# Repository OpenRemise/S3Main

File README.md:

# S3Main

<a href="https://openremise.at">
<picture>
  <source media="(prefers-color-scheme: dark)" srcset="https://github.com/OpenRemise/.github/raw/master/data/icons/icon_dark.svg">
  
</picture>
</a>

The S3Main is the first officially supported [OpenRemise](https://openremise.at) board.

### Features
- WiFi-capable ESP32-S3 SoC
- 10-22V DC supply
- Reverse polarity protection
- Single track output
- Adjustable current limits 0.5, 1.3, 2.7 and 4.1A
- [SUSI](https://normen.railcommunity.de/RCN-600.pdf) interface
- USB-C interface
- RailCom detector

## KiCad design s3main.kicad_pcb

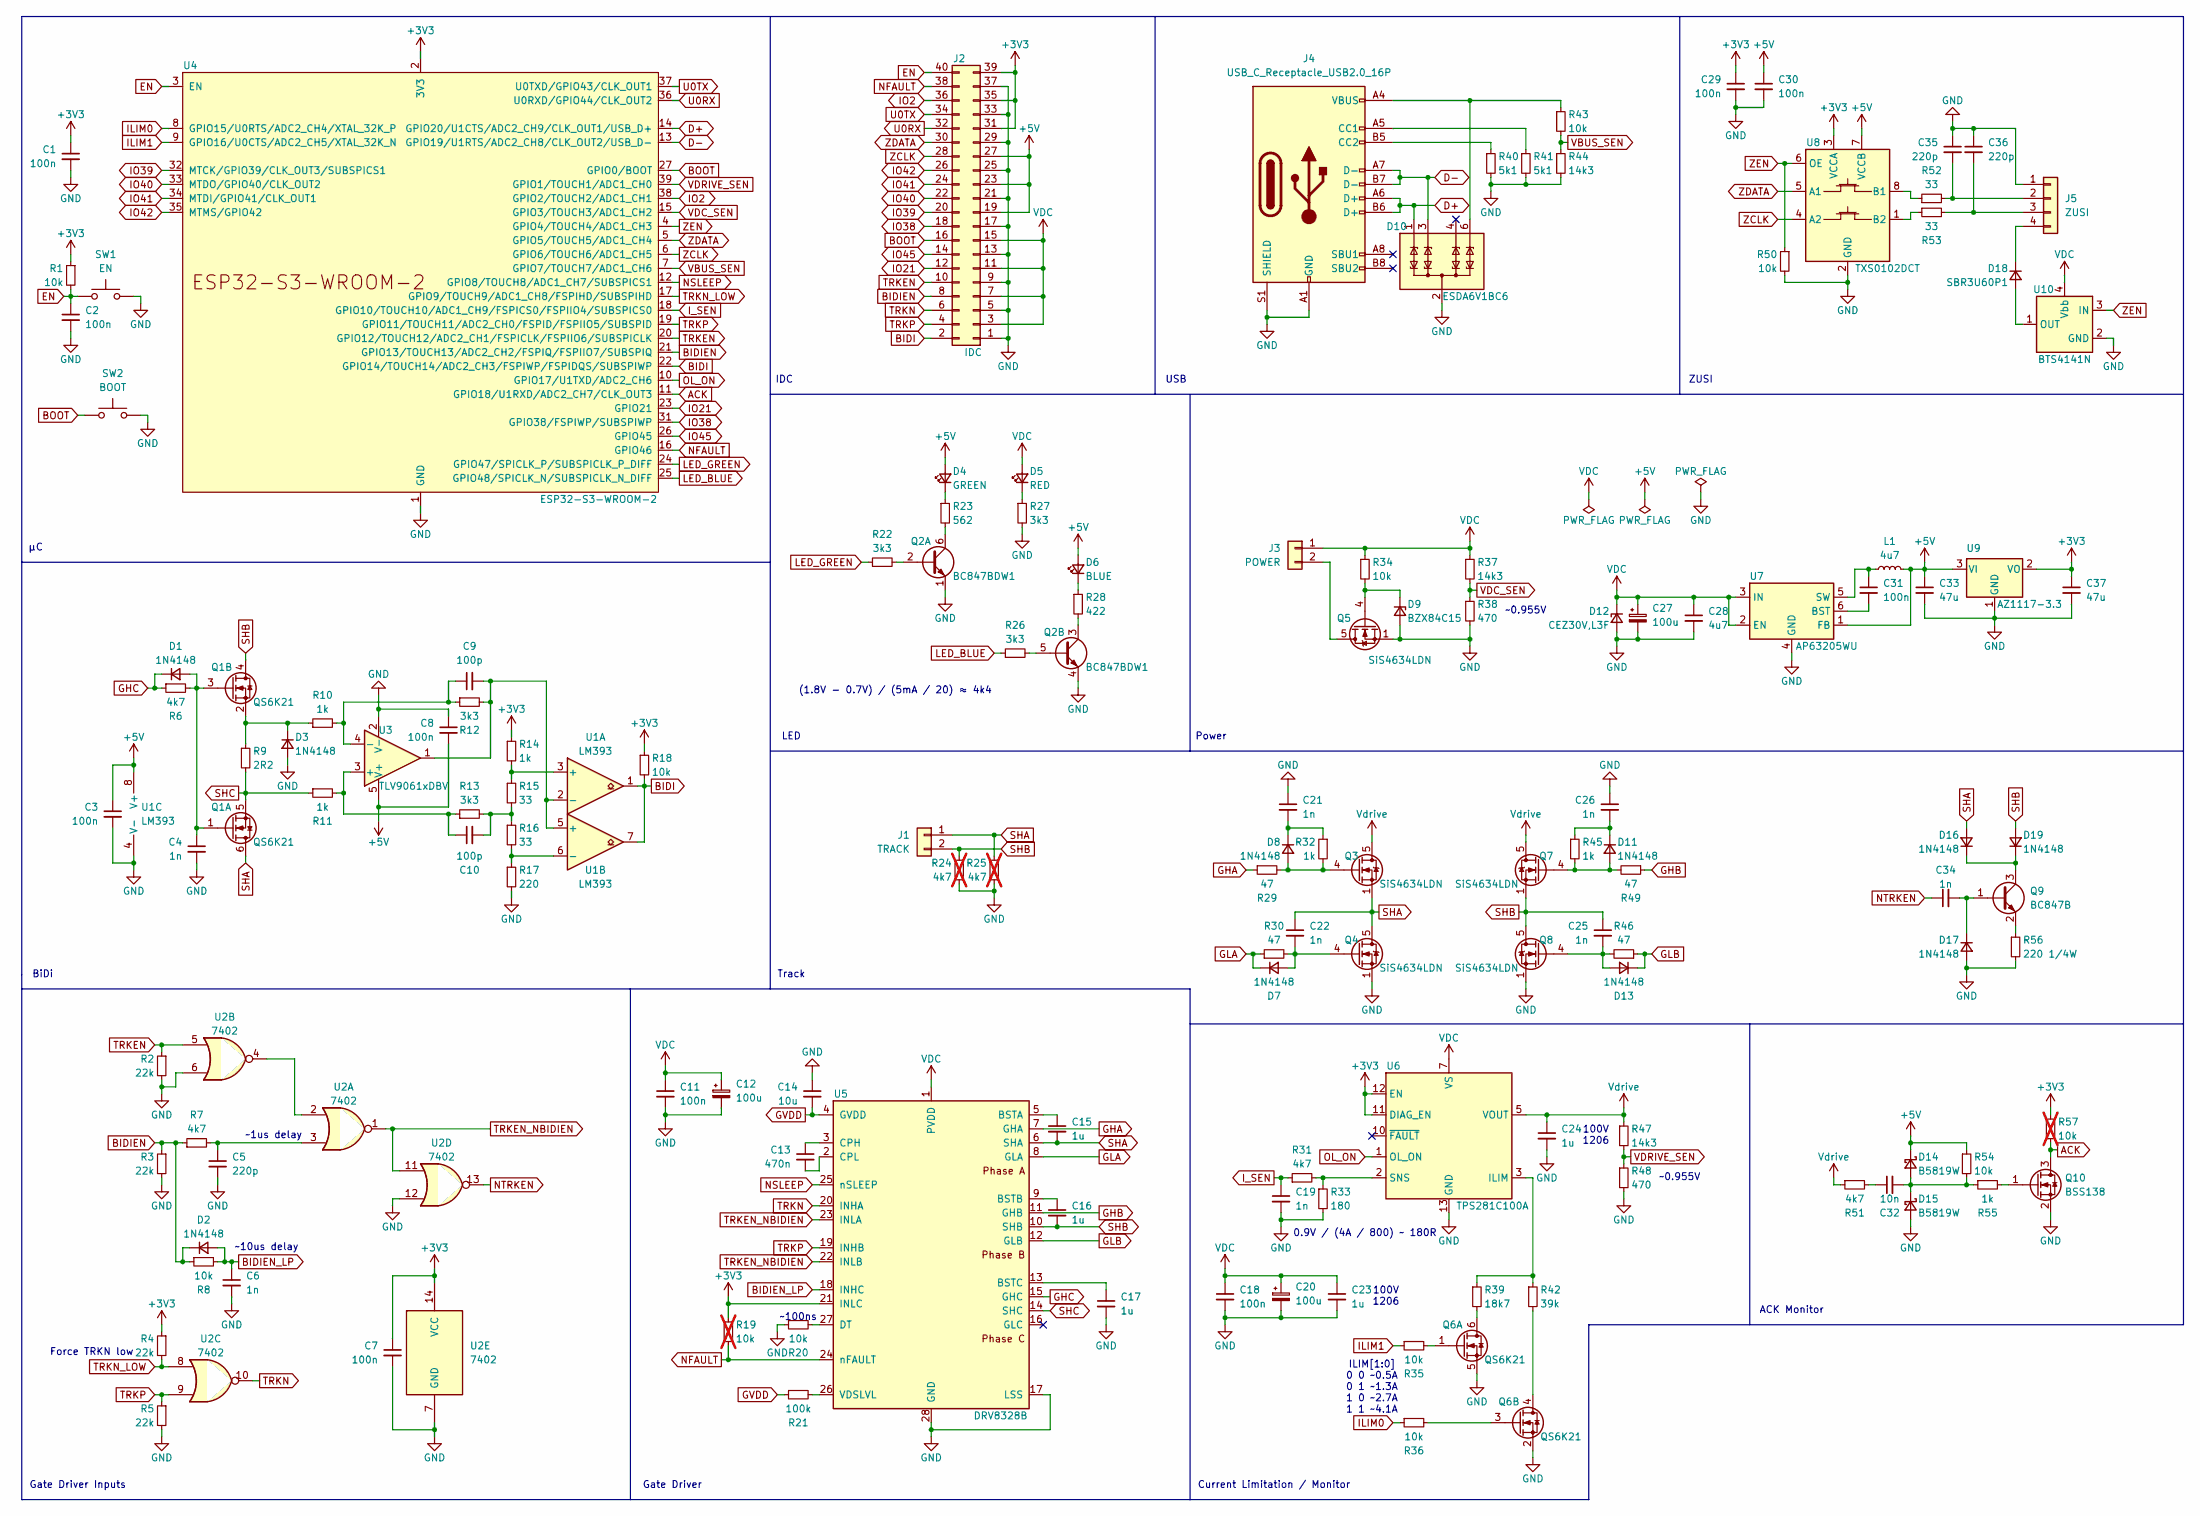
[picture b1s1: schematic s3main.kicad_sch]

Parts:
C1, C2, C3, C7, C8, C11, C18, C29, C30, C31: 100n; C_0402_1005Metric
C4, C6, C19, C21, C22, C25, C26, C34: 1n; C_0402_1005Metric
C5, C35, C36: 220p; C_0402_1005Metric
C9, C10: 100p; C_0402_1005Metric
C12, C20, C27: 100u; CP_Elec_6.3x7.7
C13: 470n; C_1206_3216Metric
C14: 10u; C_1206_3216Metric
C15, C16, C17, C23, C24: 1u; C_1206_3216Metric
C28: 4u7; C_1206_3216Metric
C32: 10n; C_1206_3216Metric
C33, C37: 47u; C_1206_3216Metric
D1, D2, D3, D7, D8, D11, D13, D16, D17, D19: 1N4148; D_SOD-523
D4: GREEN; D_0402_1005Metric
D5: RED; D_0402_1005Metric
D6: BLUE; D_0402_1005Metric
D9: BZX84C15; SOT-23
D10: ESDA6V1BC6; SOT-23-6
D12: CEZ30V,L3F; D_SOD-523
D14, D15: B5819W; D_SOD-123
D18: SBR3U60P1; D_PowerDI-123
J1: TRACK; PhoenixContact_MC_1,5_2-G-3.5_1x02_P3.50mm_Horizontal
J2: IDC; IDC-Header_2x20_P2.54mm_Vertical_SMD
J3: POWER; PhoenixContact_MC_1,5_2-G-5.08_1x02_P5.08mm_Horizontal
J4: USB_C_Receptacle_USB2.0_16P; USB_C_Receptacle_GCT_USB4105-xx-A_16P_TopMnt_Horizontal
J5: ZUSI; JST_SH_SM04B-SRSS-TB_1x04-1MP_P1.00mm_Horizontal
L1: 4u7; L_0805_2012Metric
Q1, Q6: QS6K21; TSOT-23-6
Q2: BC847BDW1; SOT-363_SC-70-6
Q3, Q4, Q5, Q7, Q8: SiS4634LDN; Vishay_PowerPAK_1212-8_Single
Q9: BC847B; SOT-23
Q10: BSS138; SOT-23
R1, R8, R18, R20, R34, R35, R36, R43, R50, R54: 10k; R_0402_1005Metric
R2, R3, R4, R5: 22k; R_0402_1005Metric
R6, R7, R31, R51: 4k7; R_0402_1005Metric
R9: 2R2; R_0805_2012Metric_Pad1.20x1.40mm_HandSolder
R10, R11, R14, R32, R45, R55: 1k; R_0402_1005Metric
R12, R13, R22, R26, R27: 3k3; R_0402_1005Metric
R15, R16, R52, R53: 33; R_0402_1005Metric
R17: 220; R_0402_1005Metric
R19, R57: 10k; R_0402_1005Metric; not fitted
R21: 100k; R_0402_1005Metric
R23: 562; R_0402_1005Metric
R24, R25: 4k7; R_0805_2012Metric_Pad1.20x1.40mm_HandSolder; not fitted
R28: 422; R_0402_1005Metric
R29, R30, R46, R49: 47; R_0402_1005Metric
R33: 180; R_0402_1005Metric
R37, R44, R47: 14k3; R_0402_1005Metric
R38, R48: 470; R_0402_1005Metric
R39: 18k7; R_0402_1005Metric
R40, R41: 5k1; R_0402_1005Metric
R42: 39k; R_0402_1005Metric
R56: 220 1/4W; R_0402_1005Metric
SW1: EN; SW_SPST_EVPBF
SW2: BOOT; SW_SPST_EVPBF
U1: LM393; SOIC-8_3.9x4.9mm_P1.27mm
U2: 7402; TSSOP-14_4.4x5mm_P0.65mm
U3: TLV9061xDBV; SOT-23-5
U4: ESP32-S3-WROOM-2
U5: DRV8328B; QFN-28-1EP_4x4mm_P0.4mm_EP2.6x2.6mm_ThermalVias
U6: TPS281C100A; WSON-12-1EP_4x4mm_P0.5mm_EP2.6x3mm_ThermalVias
U7: AP63205WU; TSOT-23-6
U8: TXS0102DCT; SSOP-8_2.95x2.8mm_P0.65mm
U9: AZ1117-3.3; SOT-89-3
U10: BTS4141N; SOT-223

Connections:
+3V3: C1.1, C7.1, C29.1, C37.1, J2.31, J2.35, J2.39, R1.1, R4.1, R14.1, R18.1, R19.1, R57.1, U2.14 (VCC), U4.2 (3V3), U5.21 (INLC), U6.11 (DIAG_EN), U6.12 (EN), U8.3 (VCCA), U9.2 (VO)
+5V: C3.1, C8.2, C30.1, C33.1, D4.2 (A), D6.2 (A), D14.1 (K), J2.19, J2.23, J2.27, L1.2, R54.1, U1.8 (V+), U3.5 (V+), U7.1 (FB), U8.7 (VCCB), U9.3 (VI)
ACK: Q10.3 (D), R57.2, U4.11 (GPIO18/U1RXD/ADC2_CH7/CLK_OUT3)
BIDI: J2.2, R18.2, U1.1, U1.7, U4.22 (GPIO14/TOUCH14/ADC2_CH3/FSPIWP/FSPIDQS/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)
BIDIEN: D2.1 (K), J2.8, R3.1, R7.1, R8.1, U4.21 (GPIO13/TOUCH13/ADC2_CH2/FSPIQ/FSPIIO7/S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)
BIDIEN_LP: C6.1, D2.2 (A), R8.2, U5.18 (INHC)
BOOT: J2.16, SW2.1, U4.27 (GPIO0/BOOT)
D+: D10.1 (TVS1), J4.A6 (D+), J4.B6 (D+), U4.14 (GPIO20/U1CTS/ADC2_CH9/CLK_OUT1/USB_D+)
D-: D10.3 (TVS2), J4.A7 (D-), J4.B7 (D-), U4.13 (GPIO19/U1RTS/ADC2_CH8/CLK_OUT2/USB_D-)
EN: C2.1, J2.40, R1.2, SW1.1, U4.3 (EN)
GHA: R29.1, U5.7 (GHA)
GHB: R49.1, U5.11 (GHB)
GHC: D1.1 (K), R6.1, U5.15 (GHC)
GLA: D7.1 (K), R30.1, U5.8 (GLA)
GLB: D13.1 (K), R46.1, U5.12 (GLB)
GND: C1.2, C2.2, C3.2, C4.2, C5.2, C6.2, C7.2, C8.1, C11.2, C12.2, C14.1, C17.2, C18.2, C19.2, C20.2, C21.1, C23.2, C24.2, C26.1, C27.2, C28.2, C29.2, C30.2, C33.2, C35.1, C36.1, C37.2, D3.2 (A), D9.2 (A), D10.2 (COM), D10.5 (COM), D12.2 (A), D15.2 (A), D17.2 (A), J2.1, J2.5, J2.9, J2.13, J2.17, J2.21, J2.25, J2.29, J2.33, J2.37, J4.A1 (GND), J4.A12 (GND), J4.B1 (GND), J4.B12 (GND), J4.S1 (SHIELD), J5.1, Q2.1 (E1), Q2.4 (E2), Q4.1 (S), Q4.2 (S), Q4.3 (S), Q5.1 (S), Q5.2 (S), Q5.3 (S), Q6.2 (S), Q6.5 (S), Q8.1 (S), Q8.2 (S), Q8.3 (S), Q10.2 (S), R2.2, R3.2, R5.2, R17.2, R20.1, R24.2, R25.2, R27.2, R33.2, R38.2, R40.2, R41.2, R44.2, R48.2, R50.2, R56.2, SW1.2, SW2.2, U1.4 (V-), U2.6, U2.7 (GND), U2.12, U3.2 (V-), U4.1 (GND), U4.40 (GND), U4.41 (GND), U5.17 (LSS), U5.28 (GND), U5.29 (GND), U6.13 (GND), U7.4 (GND), U8.2 (GND), U9.1 (GND), U10.2 (GND)
GVDD: C14.2, R21.1, U5.4 (GVDD)
ILIM0: R36.1, U4.8 (GPIO15/U0RTS/ADC2_CH4/XTAL_32K_P)
ILIM1: R35.1, U4.9 (GPIO16/U0CTS/ADC2_CH5/XTAL_32K_N)
IO2: J2.36, U4.38 (GPIO2/TOUCH2/ADC1_CH1)
IO21: J2.12, U4.23 (GPIO21)
IO38: J2.18, U4.31 (GPIO38/FSPIWP/SUBSPIWP)
IO39: J2.20, U4.32 (MTCK/GPIO39/CLK_OUT3/SUBSPICS1)
IO40: J2.22, U4.33 (MTDO/GPIO40/CLK_OUT2)
IO41: J2.24, U4.34 (MTDI/GPIO41/CLK_OUT1)
IO42: J2.26, U4.35 (MTMS/GPIO42)
IO45: J2.14, U4.26 (GPIO45)
I_SEN: C19.1, R31.1, U4.18 (GPIO10/TOUCH10/ADC1_CH9/FSPICS0/FSPIIO4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)
LED_BLUE: R26.1, U4.25 (GPIO48/SPICLK_N/SUBSPICLK_N_DIFF)
LED_GREEN: R22.1, U4.24 (GPIO47/SPICLK_P/SUBSPICLK_P_DIFF)
NFAULT: J2.38, R19.2, U4.16 (GPIO46), U5.24 (nFAULT)
NSLEEP: U4.12 (GPIO8/TOUCH8/ADC1_CH7/SUBSPICS1), U5.25 (nSLEEP)
NTRKEN: C34.1, U2.13
unnamed: C5.1, R7.2, U2.3
unnamed: C10.2, R13.2, R15.2, R16.1
unnamed: C32.1, R51.2
unnamed: C4.1, D1.2 (A), Q1.1 (G), Q1.3 (G), R6.2
unnamed: D3.1 (K), Q1.2 (S), R9.1, R10.1
unnamed: D4.1 (K), R23.1
unnamed: D5.1 (K), R27.1
unnamed: D6.1 (K), R28.1
unnamed: C22.2, D7.2 (A), Q4.4 (G), R30.2
unnamed: D8.2 (A), Q3.4 (G), R29.2, R32.2
unnamed: C21.2, D8.1 (K), R32.1
unnamed: D9.1 (K), Q5.4 (G), R34.2
unnamed: D10.6 (TVS4), J4.A4 (VBUS), J4.A9 (VBUS), J4.B4 (VBUS), J4.B9 (VBUS), R43.1
unnamed: D11.2 (A), Q7.4 (G), R45.2, R49.2
unnamed: C26.2, D11.1 (K), R45.1
unnamed: C25.2, D13.2 (A), Q8.4 (G), R46.2
unnamed: C32.2, D14.2 (A), D15.1 (K), R54.2, R55.1
unnamed: D16.1 (K), D19.1 (K), Q9.3 (C)
unnamed: C34.2, D17.1 (K), Q9.1 (B)
unnamed: D18.2 (A), U10.1 (OUT)
unnamed: D18.1 (K), J5.4
unnamed: J3.2, Q5.5 (D)
unnamed: J4.A5 (CC1), R41.1
unnamed: J4.B5 (CC2), R40.1
unnamed: C35.2, J5.2, R52.2
unnamed: C36.2, J5.3, R53.2
unnamed: Q2.2 (B1), R22.2
unnamed: Q2.6 (C1), R23.2
unnamed: Q2.5 (B2), R26.2
unnamed: Q2.3 (C2), R28.2
unnamed: Q6.6 (D), R39.2
unnamed: Q6.1 (G), R35.2
unnamed: Q6.4 (D), R42.2
unnamed: Q6.3 (G), R36.2
unnamed: Q9.2 (E), R56.1
unnamed: Q10.1 (G), R55.2
unnamed: R14.2, R15.1, U1.3 (+)
unnamed: C9.2, R12.2, U1.2 (-), U1.5 (+), U3.1
unnamed: R16.2, R17.1, U1.6 (-)
unnamed: U2.2, U2.4
unnamed: C10.1, R11.2, R13.1, U3.3 (+)
unnamed: C9.1, R10.2, R12.1, U3.4 (-)
unnamed: C15.1, U5.5 (BSTA)
unnamed: C16.1, U5.9 (BSTB)
unnamed: C17.1, U5.13 (BSTC)
unnamed: C13.1, U5.3 (CPH)
unnamed: C13.2, U5.2 (CPL)
unnamed: R20.2, U5.27 (DT)
unnamed: R21.2, U5.26 (VDSLVL)
unnamed: R39.1, R42.1, U6.3 (ILIM)
unnamed: R31.2, R33.1, U6.2 (SNS)
unnamed: C31.2, U7.6 (BST)
unnamed: C31.1, L1.1, U7.5 (SW)
unnamed: R52.1, U8.8 (B1)
unnamed: R53.1, U8.1 (B2)
OL_ON: U4.10 (GPIO17/U1TXD/ADC2_CH6), U6.1 (OL_ON)
SHA: C15.2, C22.1, D16.2 (A), J1.1, Q1.6 (D), Q3.1 (S), Q3.2 (S), Q3.3 (S), Q4.5 (D), R25.1, U5.6 (SHA)
SHB: C16.2, C25.1, D19.2 (A), J1.2, Q1.4 (D), Q7.1 (S), Q7.2 (S), Q7.3 (S), Q8.5 (D), R24.1, U5.10 (SHB)
SHC: Q1.5 (S), R9.2, R11.1, U5.14 (SHC)
TRKEN: J2.10, R2.1, U2.5, U4.20 (GPIO12/TOUCH12/ADC2_CH1/FSPICLK/FSPIIO6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)
TRKEN_NBIDIEN: U2.1, U2.11, U5.22 (INLB), U5.23 (INLA)
TRKN: J2.6, U2.10, U5.20 (INHA)
TRKN_LOW: R4.2, U2.8, U4.17 (GPIO9/TOUCH9/ADC1_CH8/FSPIHD/SUBSPIHD)
TRKP: J2.4, R5.1, U2.9, U4.19 (GPIO11/TOUCH11/ADC2_CH0/FSPID/FSPIIO5/S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), U5.19 (INHB)
U0RX: J2.32, U4.36 (U0RXD/GPIO44/CLK_OUT2)
U0TX: J2.34, U4.37 (U0TXD/GPIO43/CLK_OUT1)
VBUS_SEN: R43.2, R44.1, U4.7 (GPIO7/TOUCH7/ADC1_CH6)
VDC: C11.1, C12.1, C18.1, C20.1, C23.1, C27.1, C28.1, D5.2 (A), D12.1 (K), J2.3, J2.7, J2.11, J2.15, J3.1, R34.1, R37.1, U5.1 (PVDD), U6.7 (VS), U6.8 (VS), U7.2 (EN), U7.3 (IN), U10.4 (Vbb)
VDC_SEN: R37.2, R38.1, U4.15 (GPIO3/TOUCH3/ADC1_CH2)
VDRIVE_SEN: R47.2, R48.1, U4.39 (GPIO1/TOUCH1/ADC1_CH0)
Vdrive: C24.1, Q3.5 (D), Q7.5 (D), R47.1, R51.1, U6.5 (VOUT), U6.6 (VOUT)
ZCLK: J2.28, U4.6 (GPIO6/TOUCH6/ADC1_CH5), U8.4 (A2)
ZDATA: J2.30, U4.5 (GPIO5/TOUCH5/ADC1_CH4), U8.5 (A1)
ZEN: R50.1, U4.4 (GPIO4/TOUCH4/ADC1_CH3), U8.6 (OE), U10.3 (IN)

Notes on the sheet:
Force TRKN low
~1us delay
IDC
~0.955V
100V 1206
0.9V / (4A / 800) ~ 180R
Gate Driver
ZUSI
ILIM[1:0] 0 0 ~0.5A 0 1 ~1.3A 1 0 ~2.7A 1 1 ~4.1A
LED
Gate Driver Inputs
BiDi
USB
~100ns
Current Limitation / Monitor
Track
(1.8V - 0.7V) / (5mA / 20) ≈ 4k4
Power
~10us delay
ACK Monitor

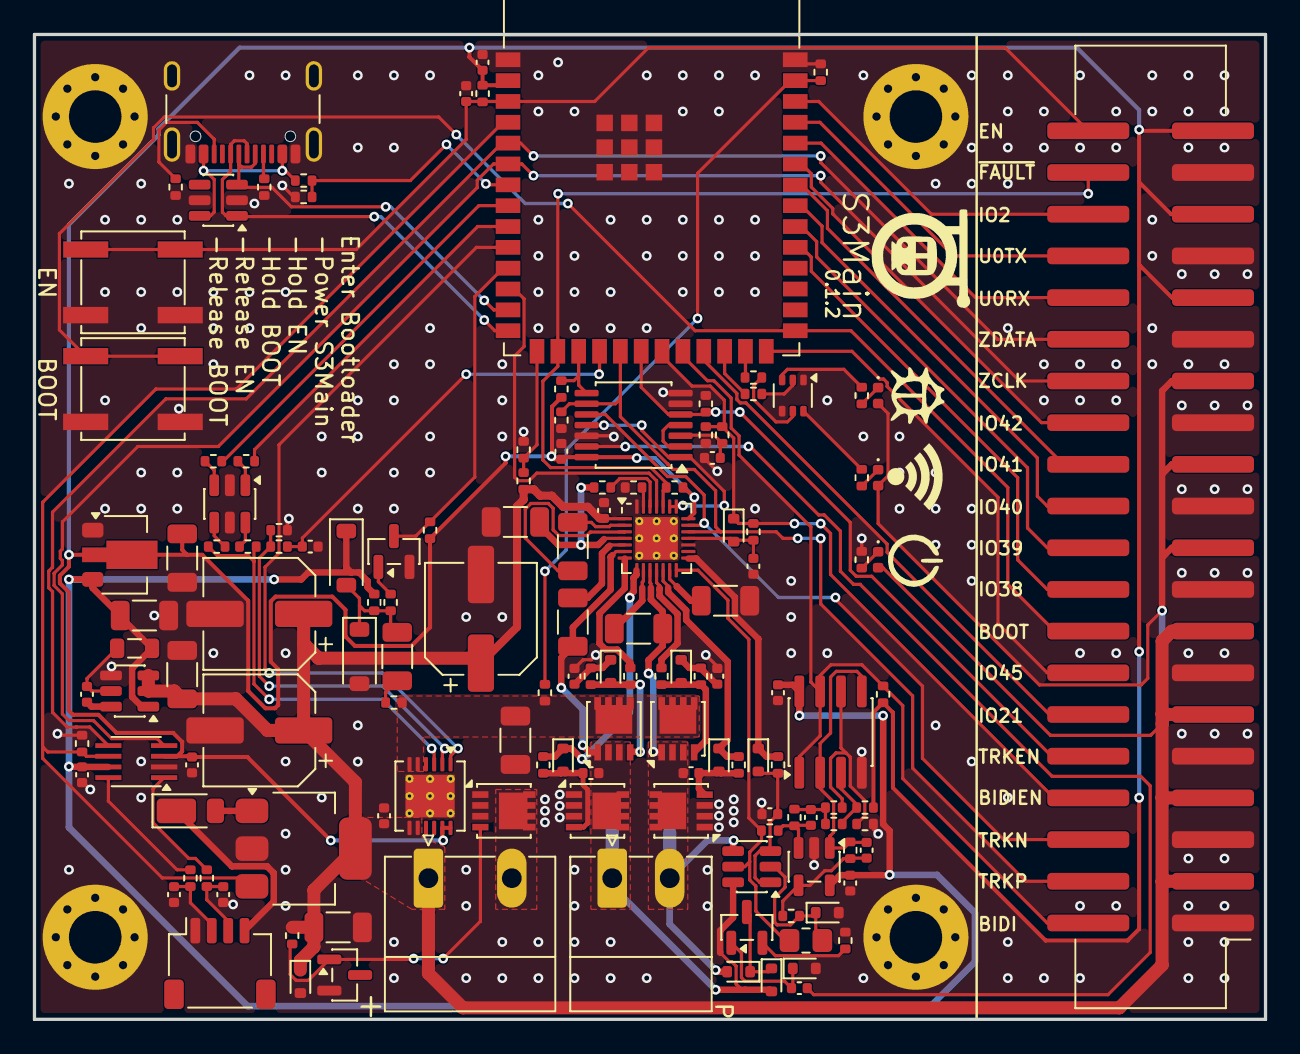
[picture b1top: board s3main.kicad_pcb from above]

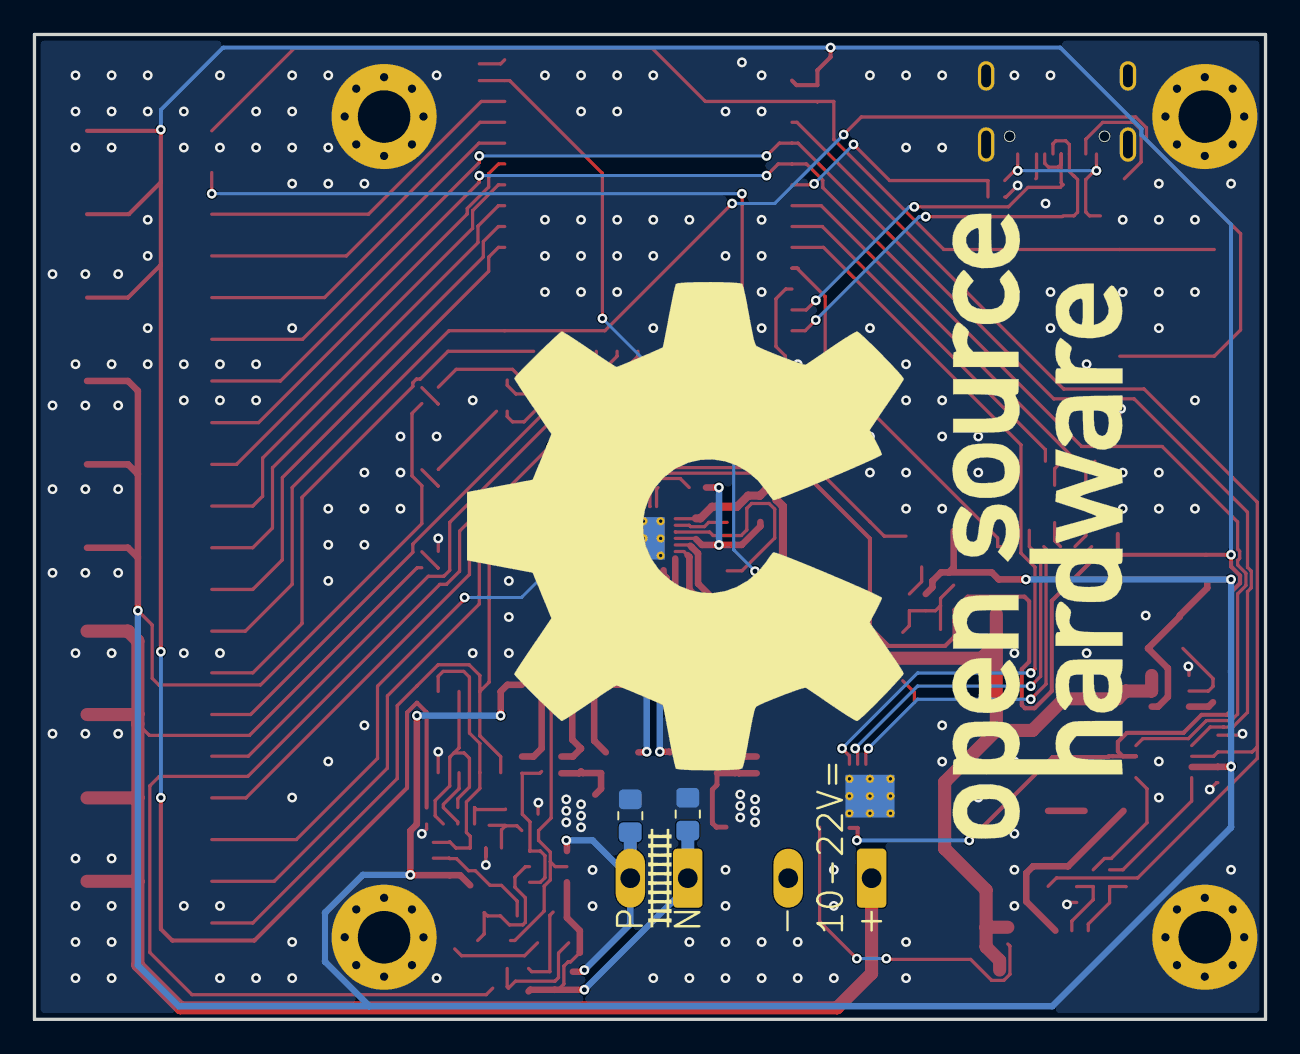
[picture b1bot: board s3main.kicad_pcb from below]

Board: 2 copper layers, 75.0 x 60.0 mm, 141 parts (2 on the bottom side), 107 nets.

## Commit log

2024-11-15 feat: revision A
2024-11-19 chore: remove R24 and R25 part number and designator in BOM
2024-11-27 chore: DNP R19
2024-11-27 chore: switch to semantic versioning
2024-12-20 feat: new ACK circuit
2024-12-21 feat: update BOM
2024-12-21 feat: update gerber
2025-01-24 docs: update README
2025-02-25 build: update to KiCad 9.0.0
2025-02-25 fix: rule "Pad Size"
2025-09-30 docs: add `Features` to README
2025-12-14 chore: replace ACK circuit with TPS28C100 fault pin
2025-12-14 chore: replace ACK circuit with TPS281C100 fault pin
2026-02-07 revert: chore: replace ACK circuit with TPS281C100 fault pin
2026-02-10 feat: replace IO2 with VDRIVE_SEN
2026-03-22 build: update to KiCad 10.0.0
2026-06-01 chore: update BOM (B5819W manufacturer)
2026-06-04 chore: use consistent SOT-23-3 footprint
2026-06-18 docs: add CHANGELOG
